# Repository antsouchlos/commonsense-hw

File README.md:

# CommonSense

A BLE-based PCB for measuring humidity and temperature.

After cloning, the libraries can be downloaded using
```bash
$ git submodule update --init
```

## PCB

## Schematic

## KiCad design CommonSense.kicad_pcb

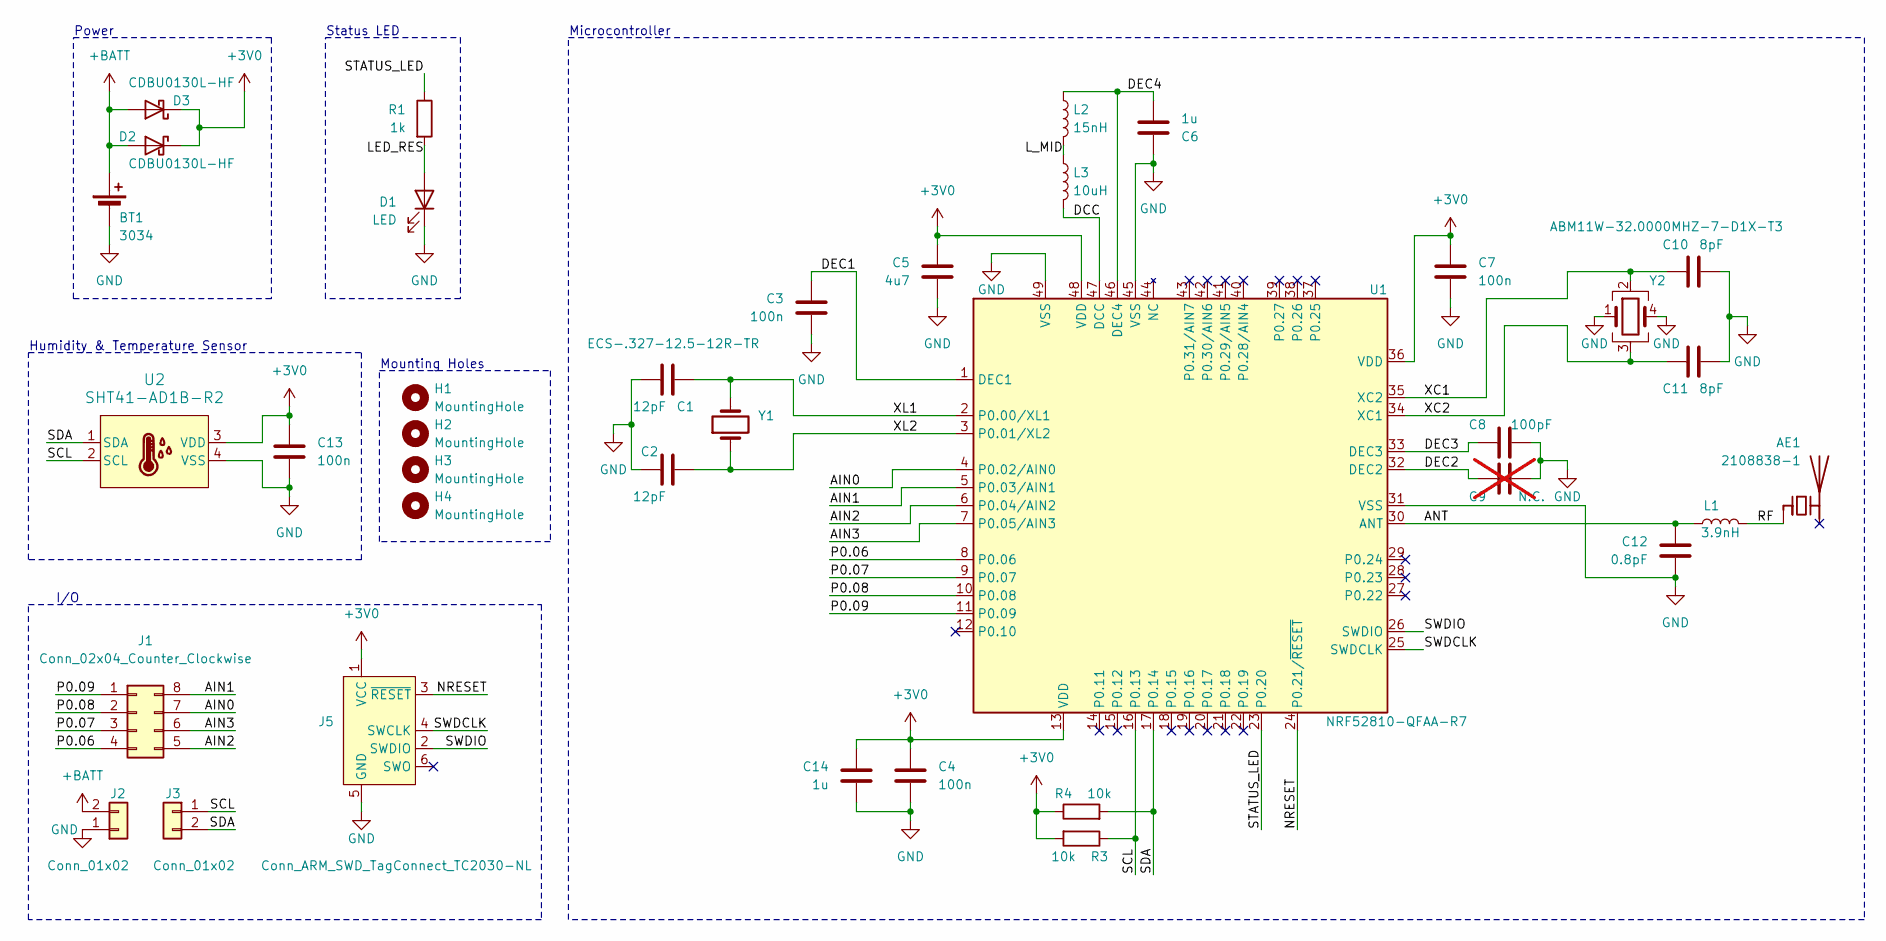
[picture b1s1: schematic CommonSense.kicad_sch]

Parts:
AE1: 2108838-1
BT1: 3034; BatteryHolder_Keystone_3034_1x20mm
C1, C2: 12pF; C_0603_1608Metric
C3, C4, C7, C13: 100n; C_0603_1608Metric
C5: 4u7; C_0603_1608Metric
C6, C14: 1u; C_0603_1608Metric
C8: 100pF; C_0603_1608Metric
C9: N.C.; C_0603_1608Metric; not fitted
C10, C11: 8pF; C_0603_1608Metric
C12: 0.8pF; C_0603_1608Metric
D1: LED; R_0603_1608Metric
D2, D3: CDBU0130L-HF; D_0603_1608Metric
H1, H2, H3, H4: MountingHole; MountingHole_2.2mm_M2
J1: Conn_02x04_Counter_Clockwise; PinHeader_2x04_P2.54mm_Vertical
J2, J3: Conn_01x02; PinHeader_1x02_P2.54mm_Vertical
J5: Conn_ARM_SWD_TagConnect_TC2030-NL; Tag-Connect_TC2030-IDC-NL_2x03_P1.27mm_Vertical
L1: 3.9nH; R_0603_1608Metric
L2: 15nH; L_0603_1608Metric
L3: 10uH; L_0603_1608Metric
R1: 1k; R_0603_1608Metric
R3, R4: 10k; R_0603_1608Metric
U1: NRF52810-QFAA-R7; QFN-48-1EP_6x6mm_P0.4mm_EP4.6x4.6mm
U2: SHT41-AD1B-R2; DFN4_SHT41_SEN
Y1: ECS-.327-12.5-12R-TR
Y2: ABM11W-32.0000MHZ-7-D1X-T3; ABM11W-30.0000MHZ-7-D1X-T3

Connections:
+3V0: C4.2, C5.2, C7.2, C13.1, C14.2, D2.1 (K), D3.1 (K), J5.1 (VCC), R3.2, R4.1, U1.13 (VDD), U1.36 (VDD), U1.48 (VDD), U2.3 (VDD)
+BATT: BT1.1 (+), D2.2 (A), D3.2 (A), J2.2
/AIN0: J1.7, U1.4 (P0.02/AIN0)
/AIN1: J1.8, U1.5 (P0.03/AIN1)
/AIN2: J1.5, U1.6 (P0.04/AIN2)
/AIN3: J1.6, U1.7 (P0.05/AIN3)
/ANT: C12.2, L1.1, U1.30 (ANT)
/DCC: L3.2, U1.47 (DCC)
/DEC1: C3.2, U1.1 (DEC1)
/DEC2: C9.1, U1.32 (DEC2)
/DEC3: C8.1, U1.33 (DEC3)
/DEC4: C6.1, L2.1, U1.46 (DEC4)
/LED_RES: D1.2 (A), R1.2
/L_MID: L2.2, L3.1
/NRESET: J5.3 (~RESET), U1.24 (P0.21/~RESET)
/P0.06: J1.4, U1.8 (P0.06)
/P0.07: J1.3, U1.9 (P0.07)
/P0.08: J1.2, U1.10 (P0.08)
/P0.09: J1.1, U1.11 (P0.09)
/RF: AE1.1 (FEED), L1.2
/SCL: J3.1, R3.1, U1.16 (P0.13), U2.2 (SCL)
/SDA: J3.2, R4.2, U1.17 (P0.14), U2.1 (SDA)
/STATUS_LED: R1.1, U1.23 (P0.20)
/SWDCLK: J5.4 (SWCLK), U1.25 (SWDCLK)
/SWDIO: J5.2 (SWDIO), U1.26 (SWDIO)
/XC1: C10.1, U1.35 (XC2), Y2.2
/XC2: C11.1, U1.34 (XC1), Y2.3
/XL1: C1.1, U1.2 (P0.00/XL1), Y1.2
/XL2: C2.1, U1.3 (P0.01/XL2), Y1.1
GND: BT1.2 (-), C1.2, C2.2, C3.1, C4.1, C5.1, C6.2, C7.1, C8.2, C9.2, C10.2, C11.2, C12.1, C13.2, C14.1, D1.1 (K), J2.1, J5.5 (GND), U1.31 (VSS), U1.45 (VSS), U1.49 (VSS), U2.4 (VSS), Y2.1, Y2.4

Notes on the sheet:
Humidity & Temperature Sensor
Microcontroller
Mounting Holes
I/O
Status LED
Power

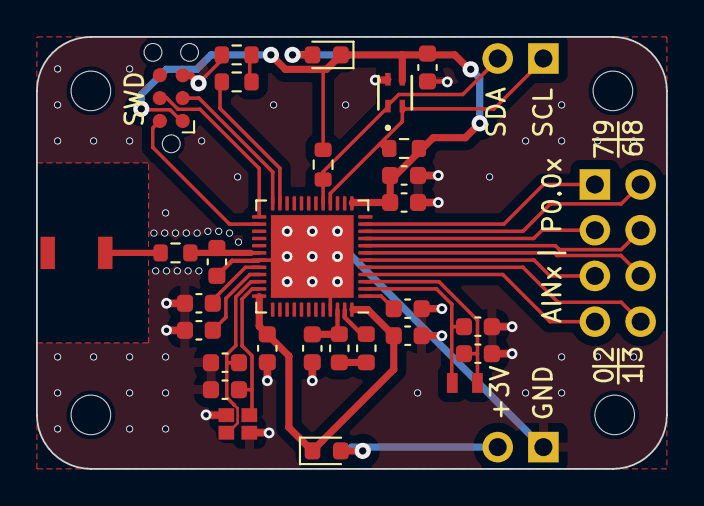
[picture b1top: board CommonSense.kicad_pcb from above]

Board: 2 copper layers, 35.0 x 24.0 mm, 37 parts (1 on the bottom side), 30 nets.

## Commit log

2023-07-29 Add project files and gitignore
2023-07-29 Add encyclopedia galactica and README.md
2023-07-29 Add lck files to gitignore
2023-07-29 Add symbol and footprint libraries to project
2023-07-29 Change librararies of components to encyclopedia galactica
2023-07-29 Check out new version of encyclopedia galactica
2023-07-29 Remove net class labels from schematic
2023-07-30 Replace schematic symbols with new versions from library
2023-07-30 Create first basic layout
2023-07-30 Add missing 3d models
2023-07-30 Fix most DRC violations
2023-07-30 Routed all connections
2023-07-30 Minor cosmetic changes
2023-07-30 Add version text
2023-07-30 Not sure what changed
2023-07-30 Tidy up schematic and add I2C pullup resistors
2023-07-30 Add I2C pullup resistors to PCB
2023-07-30 Connect IOs and AINs to pin header
2023-07-30 Start routing connections to pin header
2023-07-30 Finish routing ADC in IO pins
2023-07-30 Add SWD connector TODO to schematic
2023-07-30 Add forgotten ground vias
2023-07-30 Add 1x2 pin headers for power and I2C
2023-07-30 Position i2c and power bit headers close to other header; Add text to silk screen
2023-07-30 Move around vias
2023-07-30 Add TODO for DC/DC
2023-07-31 Add SWD connector; Add text on silkscreen
2023-07-31 Increase clearance around trace running under crystal
2023-07-31 Remove one status LED and move the other one; Fix text placement of 3V3 GND
2023-07-31 Add inductors and clean up bottom part of PCB
2023-08-01 Add reverse polarity protection diodes; Start cleaning up top part of PCB
2023-08-01 Clean up copper keepout of matching network
2023-08-01 Re-route SWD connector
2023-08-01 Add additional 1u bypass capacitor
2023-08-01 Route LED and fix silk screen warnings
2023-08-01 Add vias to avoid islands
2023-08-01 Tidy up schematic
2023-08-01 Added interactive HTML BOM output directory to gitignore
2023-08-01 Move power pin header to properly align with I2C pin header
2023-08-04 Add kiri directory to gitignore
2023-08-04 Changed Antenna icon to chip antenna and fixed designator
2023-08-04 Add antenna datasheet
2023-08-05 Change battery holder value to component number
2023-08-05 Check out newest version of library and update component
2023-08-06 Move I2C pullups closer to nrf chip; Moved I2C lines further appart
2023-08-08 Move pin headers to ensure multiple of 2.54mm spacing; Add proper via stitching
2023-08-08 Add stitching vias to RF trace
2023-08-08 Change constraints to fix design errors
2023-08-22 Change crystal capacitor values
2023-08-22 Update to newest version of library
2023-08-26 Add 1k value to LED resistor
2023-08-26 Update PCB from schematic
2023-09-07 Fix component values
2024-10-20 Add doc generation workflow (#1)
    Reviewed-on: https://git.mercurial-manifold.eu/an.tsouchlos/commonsense-hw/pulls/1
    Co-committed-by: Andreas Tsouchlos <an.tsouchlos@gmail.com>
2024-10-20 Add MIT license (#2)
    Reviewed-on: https://git.mercurial-manifold.eu/an.tsouchlos/commonsense-hw/pulls/2
    Co-committed-by: Andreas Tsouchlos <an.tsouchlos@gmail.com>
2024-10-20 Fix paths in workflow trigger (#3)
    Reviewed-on: https://git.mercurial-manifold.eu/an.tsouchlos/commonsense-hw/pulls/3
    Co-committed-by: Andreas Tsouchlos <an.tsouchlos@gmail.com>
